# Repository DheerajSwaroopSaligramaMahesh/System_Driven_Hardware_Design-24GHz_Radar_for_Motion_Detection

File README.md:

# 24GHz Motion Detection Radar

This project implements a **24 GHz radar sensor for movement detection** using **FreeSoC2 (Cypress PSoC)**, with signal processing performed through **FFT** and **CA-CFAR algorithms**.  
It integrates **hardware PCB design**, **embedded C firmware**, and **MATLAB scripts** for real-time analysis and visualization.

---

## Features
- **24 GHz Radar Frontend** – Captures reflected RF signals.
- **Analog Signal Conditioning** – Amplification + Bandpass filtering.
- **ADC Sampling** – FreeSoC2 samples the baseband signal.
- **FFT Processing** – Frequency-domain analysis on embedded side.
- **CA-CFAR Detection** – Adaptive thresholding for reliable movement detection.
- **UART Communication** – Transfers ADC/FFT/CFAR data to PC.
- **MATLAB Visualization** – Plots time-domain, FFT spectrum, and CFAR detections.
- **LED Indicators** – Show system states and detection results.

---

## Project Structure
- **C Code** → Firmware for FreeSoC2 (sampling, FFT, CFAR, UART, LEDs). [Fressoc C Code](https://github.com/DheerajSwaroopSaligramaMahesh/System_Driven_Hardware_Design-24GHz_Radar_for_Motion_Detection/tree/main/24GHz_Radar/Final_Design.cydsn/Final_Design.cydsn)
- **MATLAB Scripts** → Data acquisition & visualization of FFT + CFAR.

  [MATLAB Test Scripts](https://github.com/DheerajSwaroopSaligramaMahesh/System_Driven_Hardware_Design-24GHz_Radar_for_Motion_Detection/tree/main/24GHz_Radar/MATLAB_test_input)

  [MATLAB CFAR Script](https://github.com/DheerajSwaroopSaligramaMahesh/System_Driven_Hardware_Design-24GHz_Radar_for_Motion_Detection/blob/main/24GHz_Radar/MatlabPlots.mlx)
- **PCB Design (KiCad)** → 4-layer PCB (THT) with isolated analog/digital grounds. [KiCad PCB Design Project](https://github.com/DheerajSwaroopSaligramaMahesh/System_Driven_Hardware_Design-24GHz_Radar_for_Motion_Detection/tree/main/24GHz_Radar/PCB_Design_KiCad/Bandpass_Filter)
- **Presentation** → System explanation, testing, and results. [Presentation](https://github.com/DheerajSwaroopSaligramaMahesh/System_Driven_Hardware_Design-24GHz_Radar_for_Motion_Detection/blob/main/Final_Presentation.pdf)

---

## Workflow
1. **Signal Acquisition**  
   Radar captures reflected RF → Amplified & filtered → Converted to digital by ADC.  

2. **Embedded Processing**  
   FreeSoC2 performs FFT + CA-CFAR → Detects moving objects → LED indication.  

3. **Data Transfer & Visualization**  
   Processed data sent over UART → MATLAB plots spectrum, thresholds, and detections.  

---

## Outputs
- Hardware testing results of voltage divider, amplifiers, and ADC.  
- MATLAB plots for **sine + noise inputs, FFT magnitude, CFAR thresholds, and detected targets**.  
- Real radar detection experiments using 24 GHz module.  

---

## Files in Repo
- `C_Code/` → Embedded firmware (sampling, FFT, CFAR, UART).  
- `MATLAB/` → Scripts for simulation & visualization.  
- `Final_Presentation.pdf` → Slides showing design & testing.  

---

## Requirements
- **Hardware**: FreeSoC2 board, 24 GHz radar module, custom PCB.  
- **Software**:  
  - PSoC Creator 4.4  
  - MATLAB R2022b (or later)  

---

## How to Run
### On FreeSoC2
1. Open project in **PSoC Creator**.  
2. Build & program FreeSoC2.  
3. Press the **button** to start data acquisition.  
4. LEDs indicate **system state** (IDLE, SAMPLING, UART transfer, detection).  

### On PC (MATLAB)
1. Connect to FreeSoC2 via **UART (COM port)**.  
2. Run `MatlabPlots.mlx` in MATLAB.  
3. View **time signals, FFT spectrum, CFAR thresholds, and detections** in real-time.  

---

## References
- Project Presentation: [Final_Presentation.pdf](https://github.com/DheerajSwaroopSaligramaMahesh/System_Driven_Hardware_Design-24GHz_Radar_for_Motion_Detection/blob/main/Final_Presentation.pdf)  

---

## Project Demonstration Videos
1. [RADAR Testing Video](https://youtu.be/QEi5VdX2Rts)
2. [Final Working with CFAR](https://youtu.be/P_1PikC-du8?si=aujpoiVXmP4m2WWZ)

---

For more details, refer to the **presentation, and MATLAB/C code** in this repository.

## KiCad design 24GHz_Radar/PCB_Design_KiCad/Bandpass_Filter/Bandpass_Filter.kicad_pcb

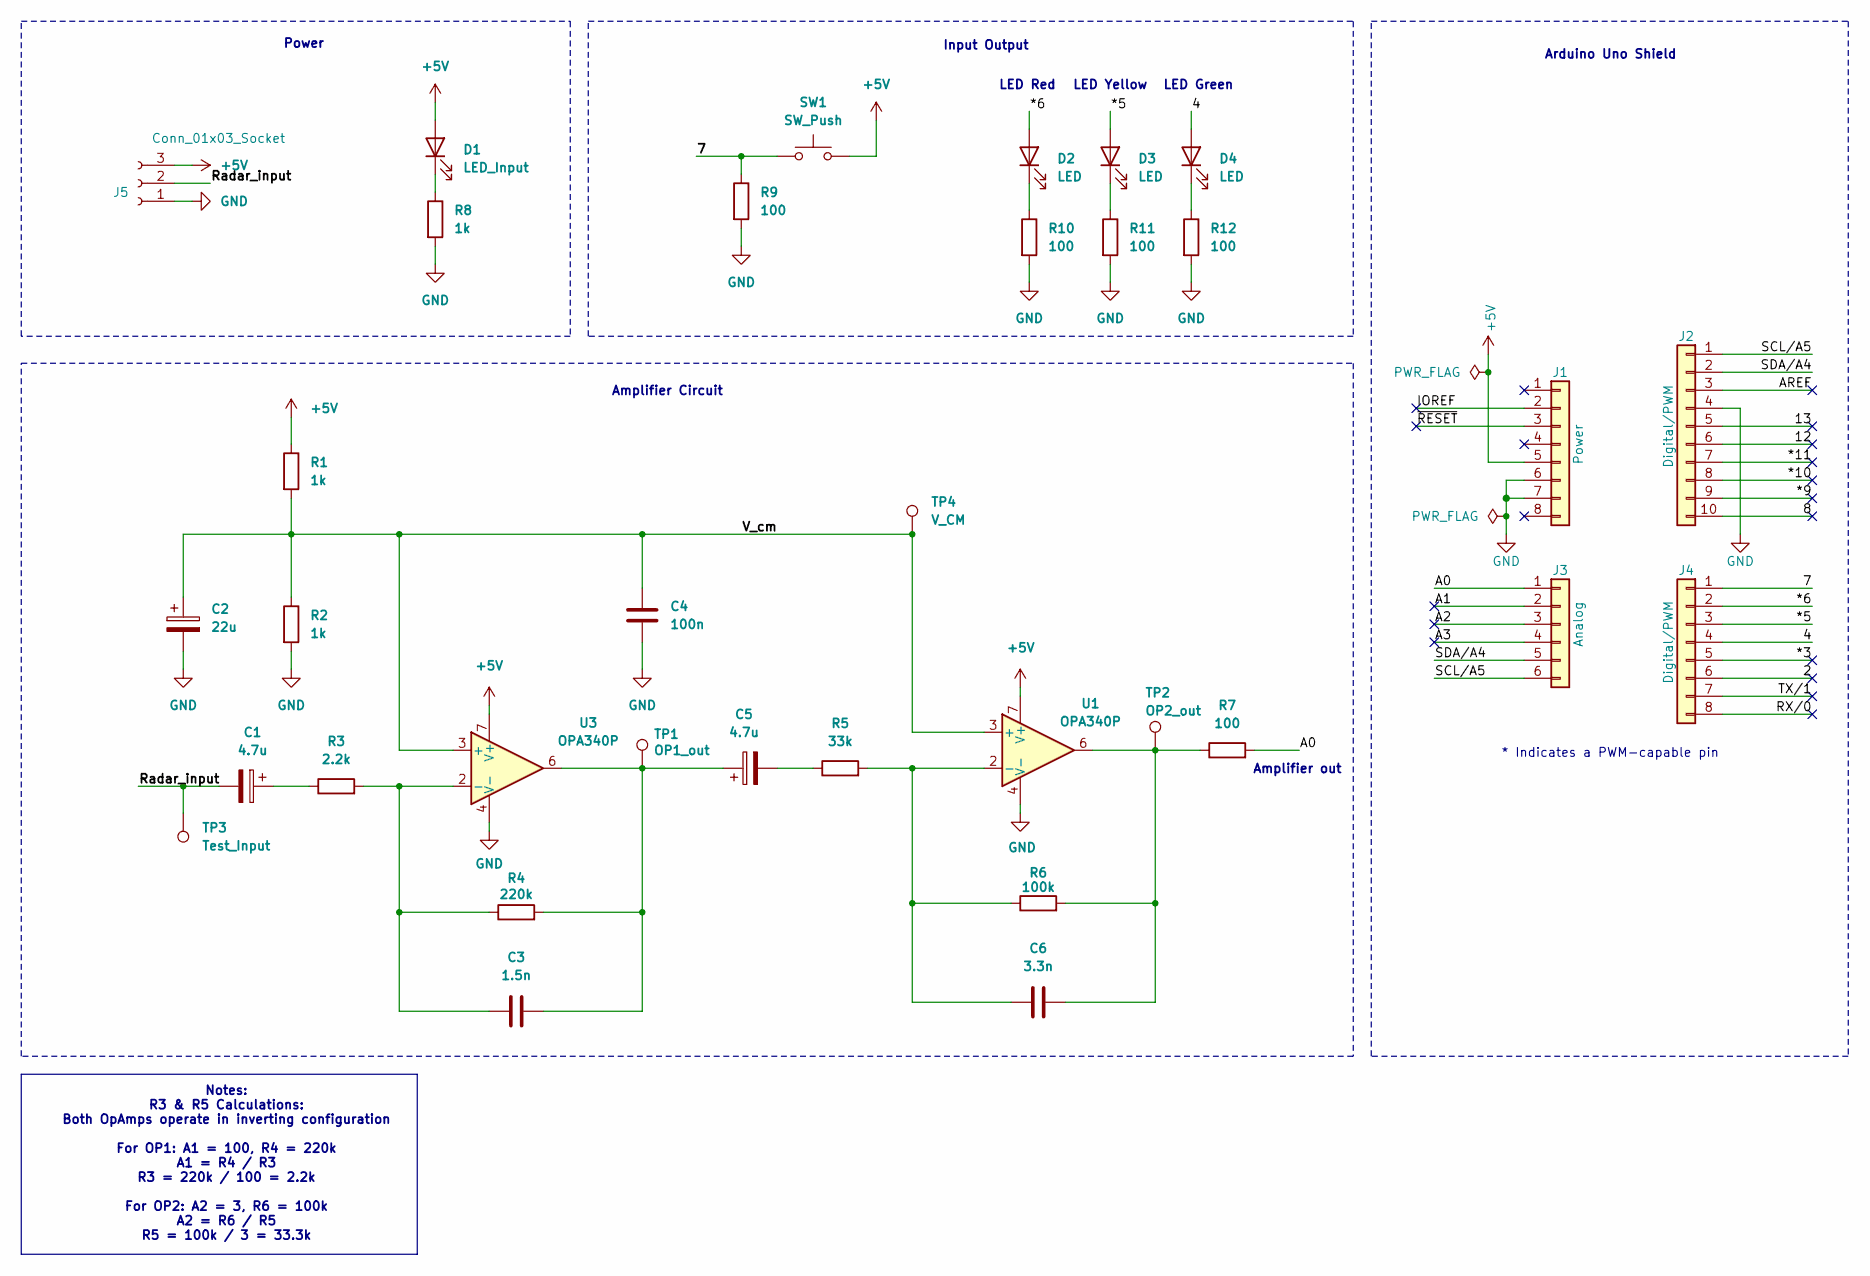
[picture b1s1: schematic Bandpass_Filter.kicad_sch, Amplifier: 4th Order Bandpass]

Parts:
C1, C5: 4.7u; CP_Radial_D6.3mm_P2.50mm
C2: 22u; CP_Radial_D5.0mm_P2.00mm
C3: 1.5n; C_Rect_L7.2mm_W7.2mm_P5.00mm_FKS2_FKP2_MKS2_MKP2
C4: 100n; C_Rect_L7.2mm_W2.5mm_P5.00mm_FKS2_FKP2_MKS2_MKP2
C6: 3.3n; C_Rect_L7.2mm_W7.2mm_P5.00mm_FKS2_FKP2_MKS2_MKP2
D1: LED_Input; LED_D5.0mm
D2, D3, D4: LED; LED_D5.0mm
J1: Power; PinSocket_1x08_P2.54mm_Vertical
J2: Digital/PWM; PinSocket_1x10_P2.54mm_Vertical
J3: Analog; PinSocket_1x06_P2.54mm_Vertical
J4: Digital/PWM; PinSocket_1x08_P2.54mm_Vertical
J5: Conn_01x03_Socket; PinSocket_1x03_P2.54mm_Horizontal
R1, R2, R8: 1k; R_Axial_DIN0207_L6.3mm_D2.5mm_P10.16mm_Horizontal
R3: 2.2k; R_Axial_DIN0207_L6.3mm_D2.5mm_P10.16mm_Horizontal
R4: 220k; R_Axial_DIN0207_L6.3mm_D2.5mm_P10.16mm_Horizontal
R5: 33k; R_Axial_DIN0207_L6.3mm_D2.5mm_P10.16mm_Horizontal
R6: 100k; R_Axial_DIN0207_L6.3mm_D2.5mm_P10.16mm_Horizontal
R7, R9, R10, R11, R12: 100; R_Axial_DIN0207_L6.3mm_D2.5mm_P10.16mm_Horizontal
SW1: SW_Push; SW_PUSH_6mm
TP1: OP1_out; PinHeader_1x01_P2.54mm_Vertical
TP2: OP2_out; PinHeader_1x01_P2.54mm_Vertical
TP3: Test_Input; PinHeader_1x01_P2.54mm_Vertical
TP4: V_CM; PinHeader_1x01_P2.54mm_Vertical
U1, U3: OPA340P; DIP-8_W7.62mm

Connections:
+5V: D1.2 (A), J1.5, J5.3, R1.1, SW1.2, U1.7 (V+), U3.7 (V+)
/2: J4.6
/4: D4.2 (A), J4.4
/7: J4.1, R9.1, SW1.1
/8: J2.10
/12: J2.6
/13: J2.5
/*3: J4.5
/*5: D3.2 (A), J4.3
/*6: D2.2 (A), J4.2
/*9: J2.9
/*10: J2.8
/*11: J2.7
/A0: J3.1, R7.2
/A1: J3.2
/A2: J3.3
/A3: J3.4
/AREF: J2.3
/IOREF: J1.2
/RX/0: J4.8
/Radar_input: C1.2, J5.2, TP3.1
/SCL/A5: J2.1, J3.6
/SDA/A4: J2.2, J3.5
/TX/1: J4.7
/V_cm: C2.1, C4.1, R1.2, R2.1, TP4.1, U1.3 (+), U3.3 (+)
/~RESET: J1.3
GND: C2.2, C4.2, J1.6, J1.7, J2.4, J5.1, R2.2, R8.2, R9.2, R10.2, R11.2, R12.2, U1.4 (V-), U3.4 (V-)
unnamed: C1.1, R3.1
unnamed: C3.2, C5.1, R4.2, TP1.1, U3.6
unnamed: C5.2, R5.1
unnamed: C6.2, R6.2, R7.1, TP2.1, U1.6
unnamed: D1.1 (K), R8.1
unnamed: D2.1 (K), R10.1
unnamed: D3.1 (K), R11.1
unnamed: D4.1 (K), R12.1
unnamed: C6.1, R5.2, R6.1, U1.2 (-)
unnamed: C3.1, R3.2, R4.1, U3.2 (-)

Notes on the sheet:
Amplifier Circuit
LED Green
Notes: R3 & R5 Calculations: Both OpAmps operate in inverting configuration For OP1: A1 = 100, R4 = 220k A1 = R4 / R3 R3 = 220k / 100 = 2.2k For OP2: A2 = 3, R6 = 100k A2 = R6 / R5 R5 = 100k / 3 = 33.3k
LED Red
Power
Arduino Uno Shield
LED Yellow
* Indicates a PWM-capable pin
Input Output
Amplifier out

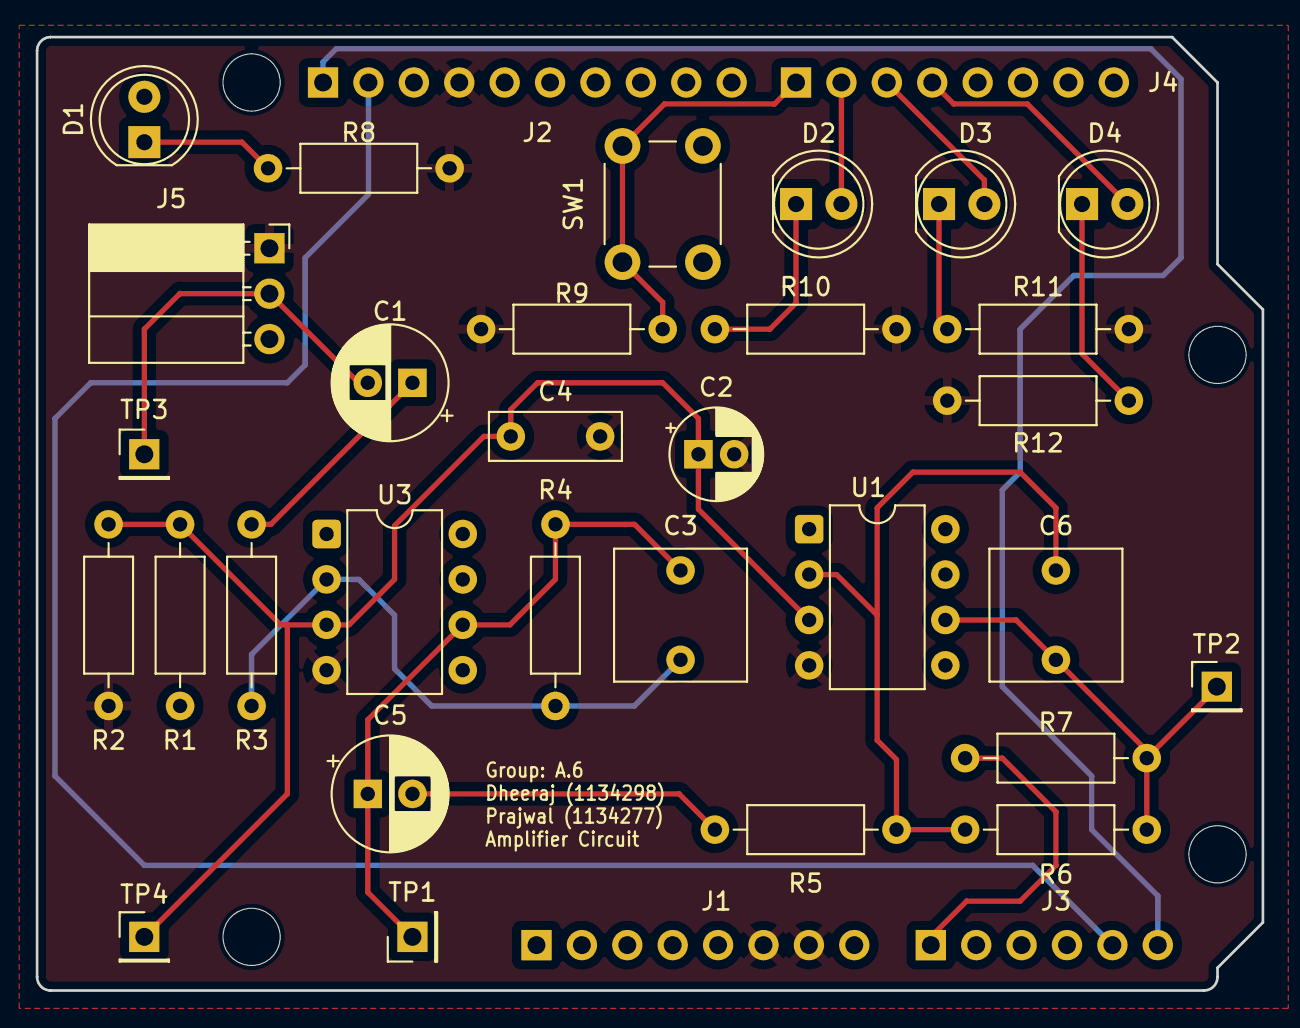
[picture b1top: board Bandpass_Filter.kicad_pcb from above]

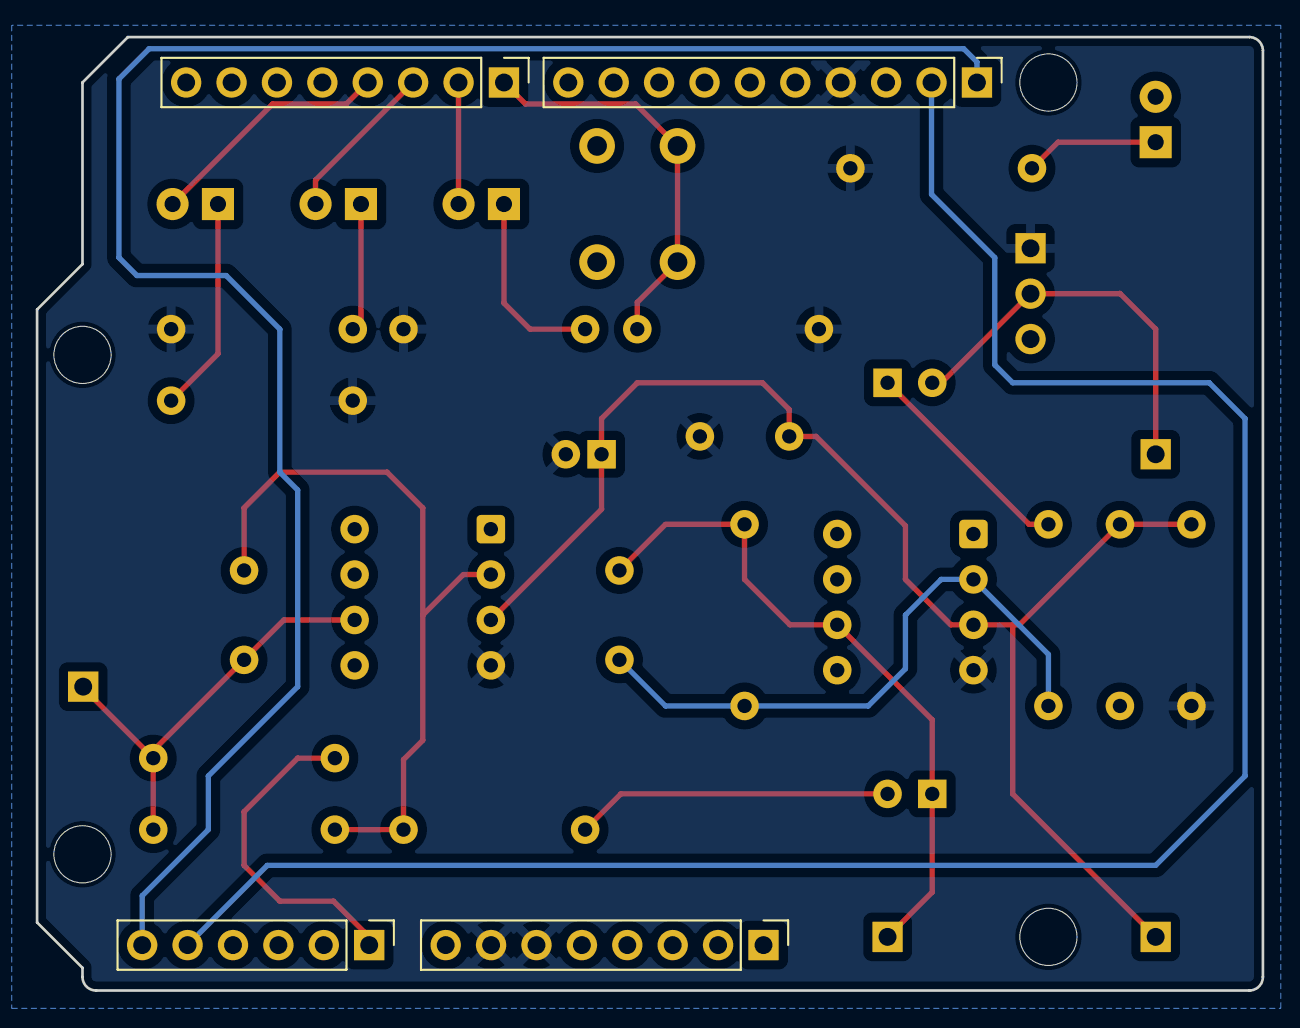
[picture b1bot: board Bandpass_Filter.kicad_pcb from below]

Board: 4 copper layers, 68.6 x 53.3 mm, 38 parts (4 on the bottom side), 21 nets.

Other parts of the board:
MH1, MH2, MH3, MH4: MountingHole_3.2mm

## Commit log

2025-08-30 Update project workspace file
